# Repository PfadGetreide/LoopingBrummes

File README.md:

# Looping Brummes
Looping Louie is a game of skill for children produced by Milton Bradley since 
1994 (<a href="https://en.wikipedia.org/wiki/Loopin'_Louie">Wikipedia</a>).
Abused and very popular among alcoholics at parties, was it my intention to 
modify and personalize this game.The outcome is called "Looping Brummes". 
The main function of this mod is to control the speed of the little guy flying 
in circles. In addition there is the possibility to randomize the speed and even
the direction.

This repository mod consist of the following:
<ul>
  <li>KiCAD files for the PCB</li>
  <li>source code for the controls</li>
  <li>3D-models for the case and the lighting mod</li>
</ul> 

# KiCAD
One part of the project is a custom PCB containing a DC-motor controller, a 
step-up converter needed for more speed, a SSD1306 display, a rotary encoder for
menu navigation and a place to solder down a RaspberryPi Pico.

# Source Code
The code is still under construction.But it works :)
Any tips are welcome.

# 3D-models
The models are the case with a top and bottom piece and a mod to hide a LED strip
on the base of the Looping Louie.
For the case, you will need 4 M4 heat inserts and 4 M4x10 screws.

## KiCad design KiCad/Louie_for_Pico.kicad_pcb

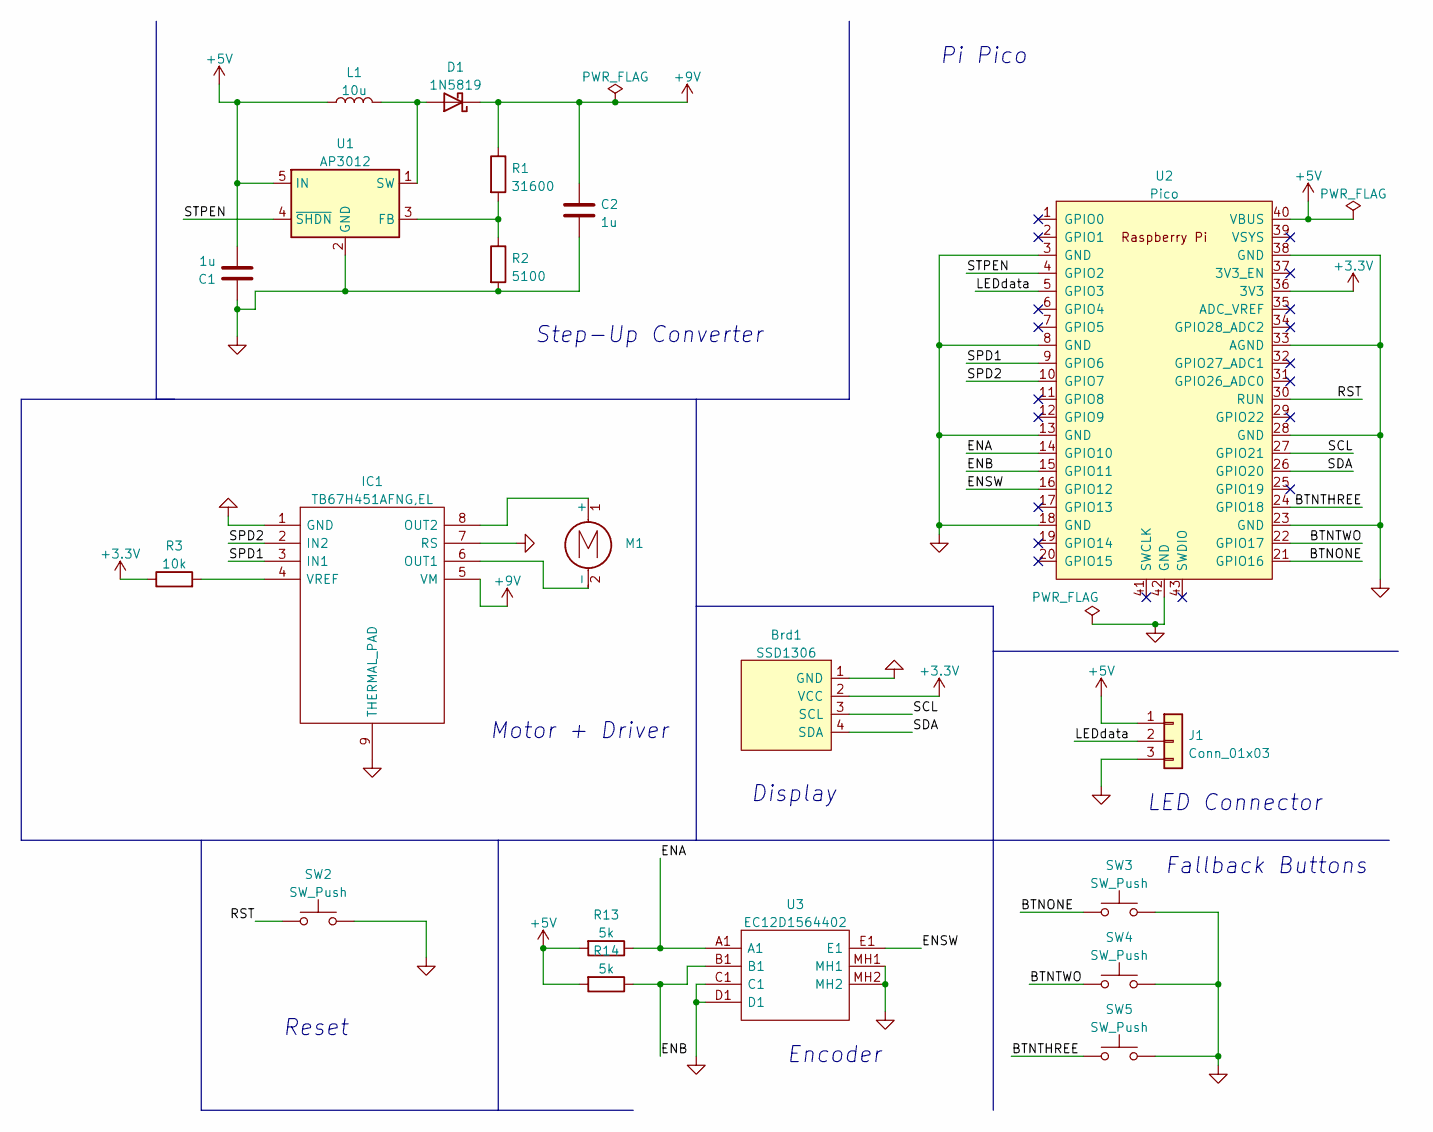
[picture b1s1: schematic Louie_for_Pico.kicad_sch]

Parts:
Brd1: SSD1306; SSD1306-0.91-OLED-4pin-128x32
C1, C2: 1u; C_1206_3216Metric_Pad1.33x1.80mm_HandSolder
D1: 1N5819; D_SOD-123F
IC1: TB67H451AFNG,EL; SOIC127P600X170-9N; Mouser Part Number 757-TB67H451AFNGEL
J1: Conn_01x03; Molex_KK-254_AE-6410-03A_1x03_P2.54mm_Vertical
L1: 10u; L_Taiyo-Yuden_NR-40xx_HandSoldering
M1: Molex_KK-254_AE-6410-02A_1x02_P2.54mm_Vertical
R1: 31600; R_1206_3216Metric_Pad1.30x1.75mm_HandSolder
R2: 5100; R_1206_3216Metric_Pad1.30x1.75mm_HandSolder
R3: 10k; R_1206_3216Metric_Pad1.30x1.75mm_HandSolder
R13, R14: 5k; R_1206_3216Metric_Pad1.30x1.75mm_HandSolder
SW2, SW3, SW4, SW5: SW_Push; SW_TH_Tactile_Omron_B3F-10xx
U1: AP3012; SOT-23-5
U2: Pico; RPi_Pico_SMD_TH
U3: EC12D1564402; Mouser Part Number 688-EC12D1564402

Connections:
+3V3: Brd1.2 (VCC), R3.1, U2.36 (3V3)
+5V: C1.2, J1.1, L1.1, R13.2, R14.2, U1.5 (IN), U2.40 (VBUS)
+9V: C2.1, D1.1 (K), IC1.5 (VM), R1.1
/BTNONE: SW3.1, U2.21 (GPIO16)
/BTNTHREE: SW5.1, U2.24 (GPIO18)
/BTNTWO: SW4.1, U2.22 (GPIO17)
/ENA: R13.1, U2.14 (GPIO10), U3.A1
/ENB: R14.1, U2.15 (GPIO11), U3.B1
/ENSW: U2.16 (GPIO12), U3.E1
/LEDdata: J1.2, U2.5 (GPIO3)
/RST: SW2.1, U2.30 (RUN)
/SCL: Brd1.3 (SCL), U2.27 (GPIO21)
/SDA: Brd1.4 (SDA), U2.26 (GPIO20)
/SPD1: IC1.3 (IN1), U2.9 (GPIO6)
/SPD2: IC1.2 (IN2), U2.10 (GPIO7)
/STPEN: U1.4 (~SHDN), U2.4 (GPIO2)
GND: Brd1.1 (GND), C1.1, C2.2, IC1.1 (GND), IC1.7 (RS), IC1.9 (THERMAL_PAD), J1.3, R2.2, SW2.2, SW3.2, SW4.2, SW5.2, U1.2 (GND), U2.3 (GND), U2.8 (GND), U2.13 (GND), U2.18 (GND), U2.23 (GND), U2.28 (GND), U2.33 (AGND), U2.38 (GND), U2.42 (GND), U3.C1, U3.D1, U3.MH1, U3.MH2
unnamed: D1.2 (A), L1.2, U1.1 (SW)
unnamed: IC1.4 (VREF), R3.2
unnamed: IC1.6 (OUT1), M1.2 (-)
unnamed: IC1.8 (OUT2), M1.1 (+)
unnamed: R1.2, R2.1, U1.3 (FB)

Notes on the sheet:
Pi Pico
Display
LED Connector
Encoder
Motor + Driver
Fallback Buttons
Step-Up Converter
Reset

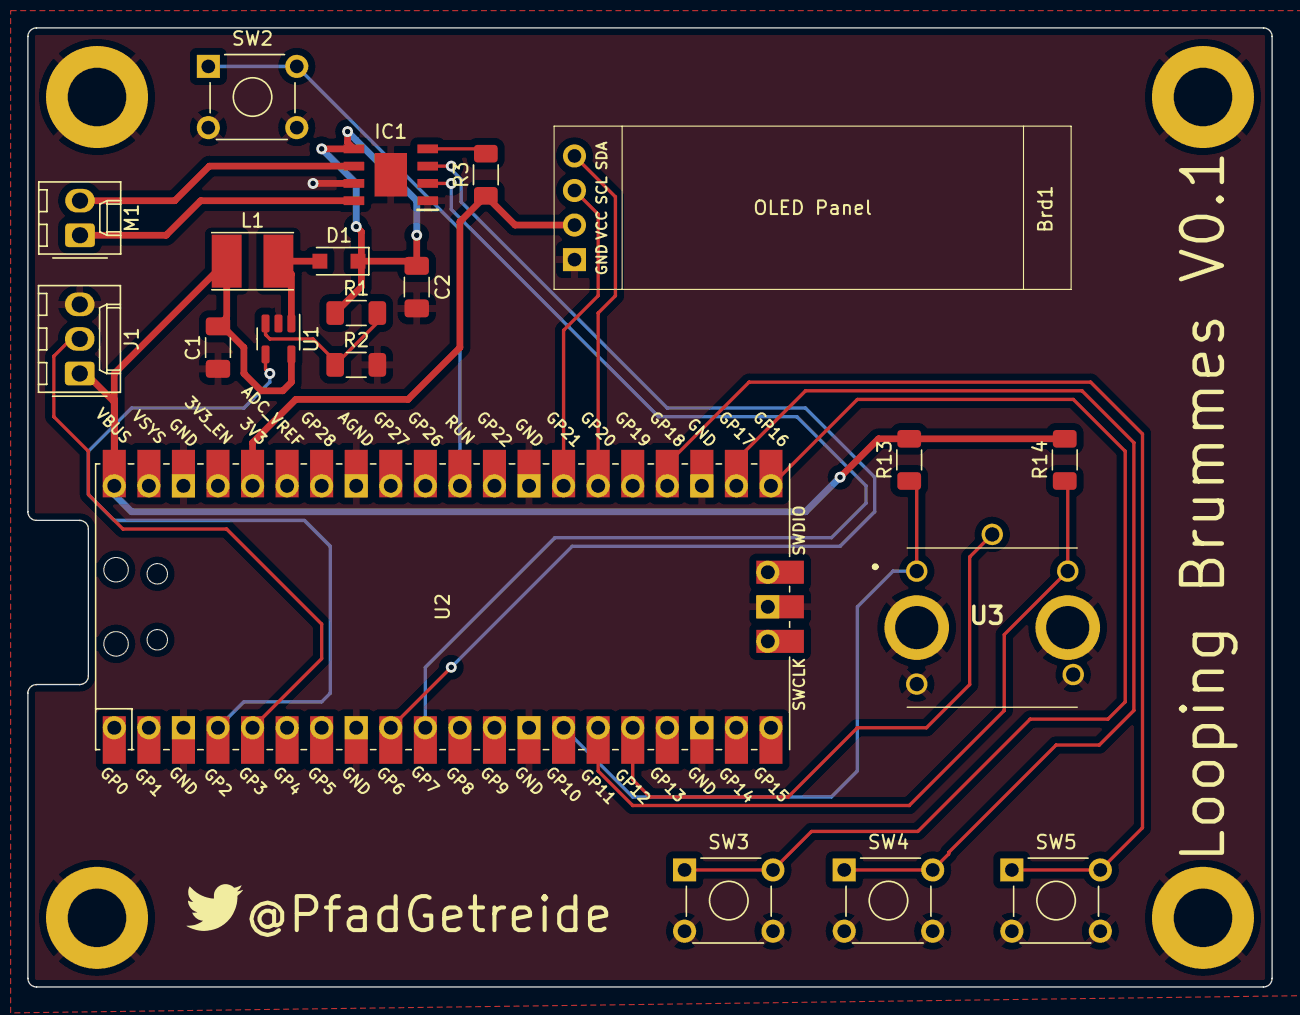
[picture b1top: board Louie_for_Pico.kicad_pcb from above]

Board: 2 copper layers, 91.4 x 70.5 mm, 20 parts (0 on the bottom side), 22 nets.

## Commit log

2023-04-13 Initialer Commit
2023-04-13 geändert: README.md
2023-04-13 wire edit
2023-04-16 3d models, kicad, geting code running w platformio
2023-04-17 clean up
2023-04-17 readme edit
2023-04-17 formatting
2023-04-20 more readme
2023-04-28 major comment update
2023-04-28 comments added
